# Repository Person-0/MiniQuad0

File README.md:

# **MiniQuad0**
Tiny Brushless Quadcopter, smaller and simpler version of Quad0.<br>
Custom flight controller with self-assembly in mind.

## 😼💖

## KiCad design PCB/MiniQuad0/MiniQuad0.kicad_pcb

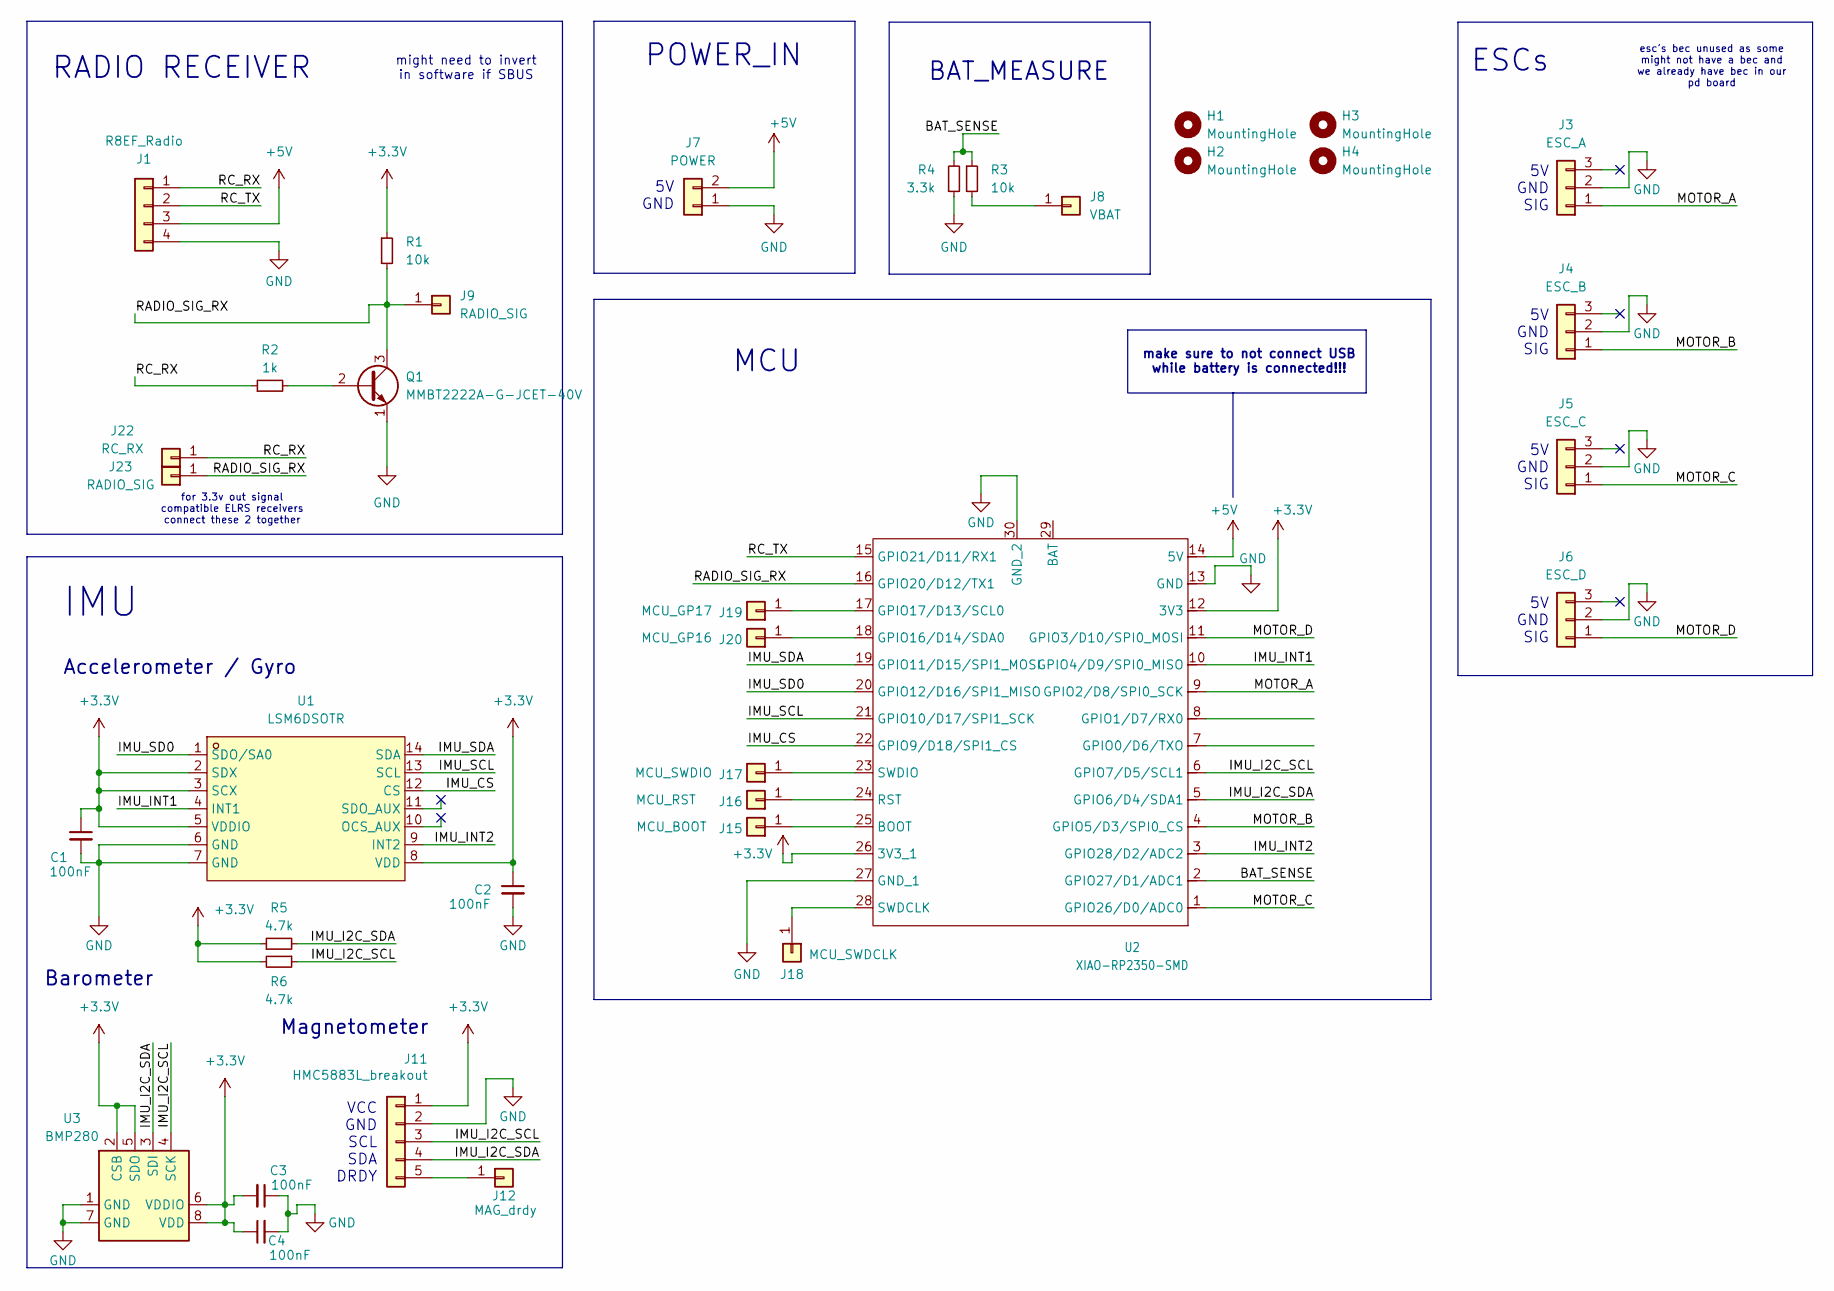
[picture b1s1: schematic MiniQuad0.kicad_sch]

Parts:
C1, C2, C3, C4: 100nF; C_0603_1608Metric_Pad1.08x0.95mm_HandSolder
H1, H2, H3, H4: MountingHole; MountingHole_3mm
J1: R8EF_Radio; PinHeader_1x04_P2.54mm_Vertical
J3: ESC_A; PinHeader_1x03_P2.54mm_Vertical
J4: ESC_B; PinHeader_1x03_P2.54mm_Vertical
J5: ESC_C; PinHeader_1x03_P2.54mm_Vertical
J6: ESC_D; PinHeader_1x03_P2.54mm_Vertical
J7: POWER; PinHeader_1x02_P2.54mm_Vertical
J8: VBAT; PinHeader_1x01_P2.54mm_Vertical
J9, J23: RADIO_SIG; TestPoint_Pad_D1.0mm
J11: HMC5883L_breakout; PinHeader_1x05_P2.54mm_Vertical
J12: MAG_drdy; TestPoint_Pad_D1.0mm
J15: MCU_BOOT; TestPoint_Pad_D1.0mm
J16: MCU_RST; TestPoint_Pad_D1.0mm
J17: MCU_SWDIO; TestPoint_Pad_D1.0mm
J18: MCU_SWDCLK; TestPoint_Pad_D1.0mm
J19: MCU_GP17; TestPoint_Pad_D1.0mm
J20: MCU_GP16; TestPoint_Pad_D1.0mm
J22: RC_RX; TestPoint_Pad_D1.0mm
Q1: MMBT2222A-G-JCET-40V; TSOT-23_HandSoldering
R1, R3: 10k; R_1206_3216Metric_Pad1.30x1.75mm_HandSolder
R2: 1k; R_1206_3216Metric_Pad1.30x1.75mm_HandSolder
R4: 3.3k; R_1206_3216Metric_Pad1.30x1.75mm_HandSolder
R5, R6: 4.7k; R_1206_3216Metric_Pad1.30x1.75mm_HandSolder
U1: LSM6DSOTR; LGA-14_L3.0-W2.5-P0.50-TL; MPN LSM6DSOTR; LCSC Part C2655100
U2: XIAO-RP2350-SMD
U3: BMP280; Bosch_LGA-8_2x2.5mm_P0.65mm_ClockwisePinNumbering

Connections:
+3.3V: C1.1, C2.1, C3.2, C4.1, J11.1, R1.1, R5.1, R6.2, U1.2 (SDX), U1.3 (SCX), U1.5 (VDDIO), U1.8 (VDD), U2.12 (3V3), U2.26 (3V3_1), U3.2 (CSB), U3.5 (SDO), U3.6 (VDDIO), U3.8 (VDD)
+5V: J1.3, J7.2, U2.14 (5V)
/BAT_SENSE: R3.1, R4.2, U2.2 (GPIO27/D1/ADC1)
/IMU_CS: U1.12 (CS), U2.22 (GPIO9/D18/SPI1_CS)
/IMU_I2C_SCL: J11.3, R6.1, U2.6 (GPIO7/D5/SCL1), U3.4 (SCK)
/IMU_I2C_SDA: J11.4, R5.2, U2.5 (GPIO6/D4/SDA1), U3.3 (SDI)
/IMU_INT1: U1.4 (INT1), U2.10 (GPIO4/D9/SPI0_MISO)
/IMU_INT2: U1.9 (INT2), U2.3 (GPIO28/D2/ADC2)
/IMU_SCL: U1.13 (SCL), U2.21 (GPIO10/D17/SPI1_SCK)
/IMU_SD0: U1.1 (SDO/SA0), U2.20 (GPIO12/D16/SPI1_MISO)
/IMU_SDA: U1.14 (SDA), U2.19 (GPIO11/D15/SPI1_MOSI)
/MOTOR_A: J3.1, U2.9 (GPIO2/D8/SPI0_SCK)
/MOTOR_B: J4.1, U2.4 (GPIO5/D3/SPI0_CS)
/MOTOR_C: J5.1, U2.1 (GPIO26/D0/ADC0)
/MOTOR_D: J6.1, U2.11 (GPIO3/D10/SPI0_MOSI)
/RADIO_SIG_RX: J9.1, J23.1, Q1.3 (C), R1.2, U2.16 (GPIO20/D12/TX1)
/RC_RX: J1.1, J22.1, R2.1
/RC_TX: J1.2, U2.15 (GPIO21/D11/RX1)
GND: C1.2, C2.2, C3.1, C4.2, J1.4, J3.2, J4.2, J5.2, J6.2, J7.1, J11.2, Q1.1 (E), R4.1, U1.6 (GND), U1.7 (GND), U2.13 (GND), U2.27 (GND_1), U2.30 (GND_2), U3.1 (GND), U3.7 (GND)
unnamed: J8.1, R3.2
unnamed: J11.5, J12.1
unnamed: J15.1, U2.25 (BOOT)
unnamed: J16.1, U2.24 (RST)
unnamed: J17.1, U2.23 (SWDIO)
unnamed: J18.1, U2.28 (SWDCLK)
unnamed: J19.1, U2.17 (GPIO17/D13/SCL0)
unnamed: J20.1, U2.18 (GPIO16/D14/SDA0)
unnamed: Q1.2 (B), R2.2

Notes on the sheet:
Accelerometer / Gyro
esc's bec unused as some might not have a bec and we already have bec in our pd board
IMU
Barometer
RADIO RECEIVER
make sure to not connect USB while battery is connected!!!
5V GND SIG
BAT_MEASURE
Magnetometer
POWER_IN
ESCs
MCU
for 3.3v out signal compatible ELRS receivers connect these 2 together
VCC GND SCL SDA DRDY
might need to invert in software if SBUS
5V GND

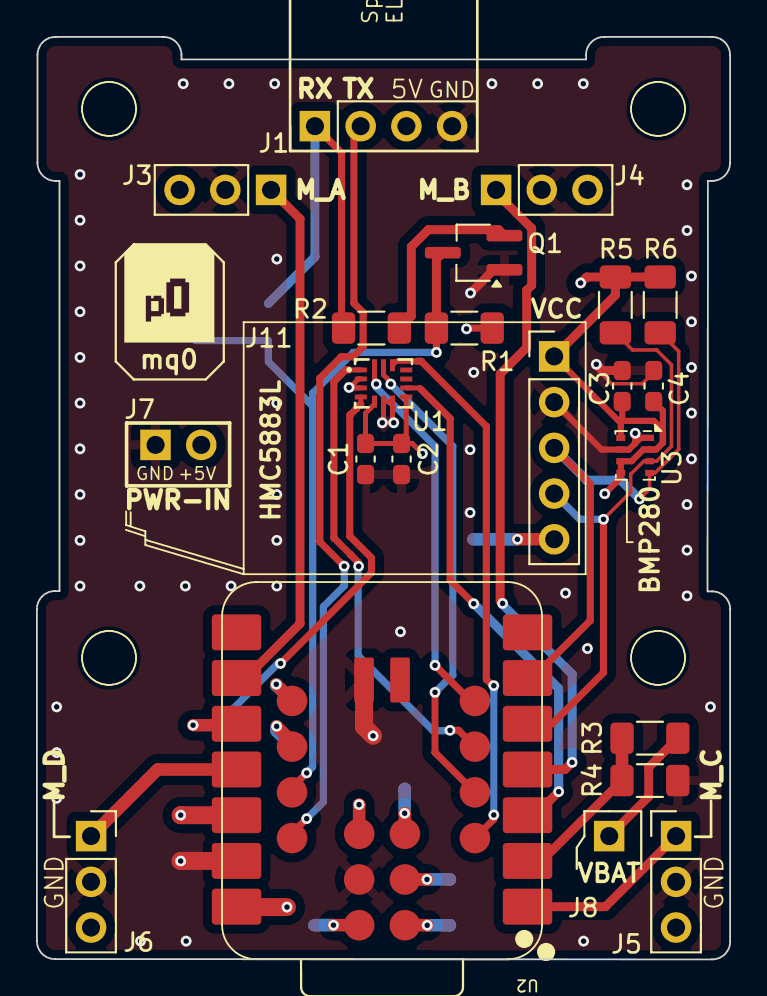
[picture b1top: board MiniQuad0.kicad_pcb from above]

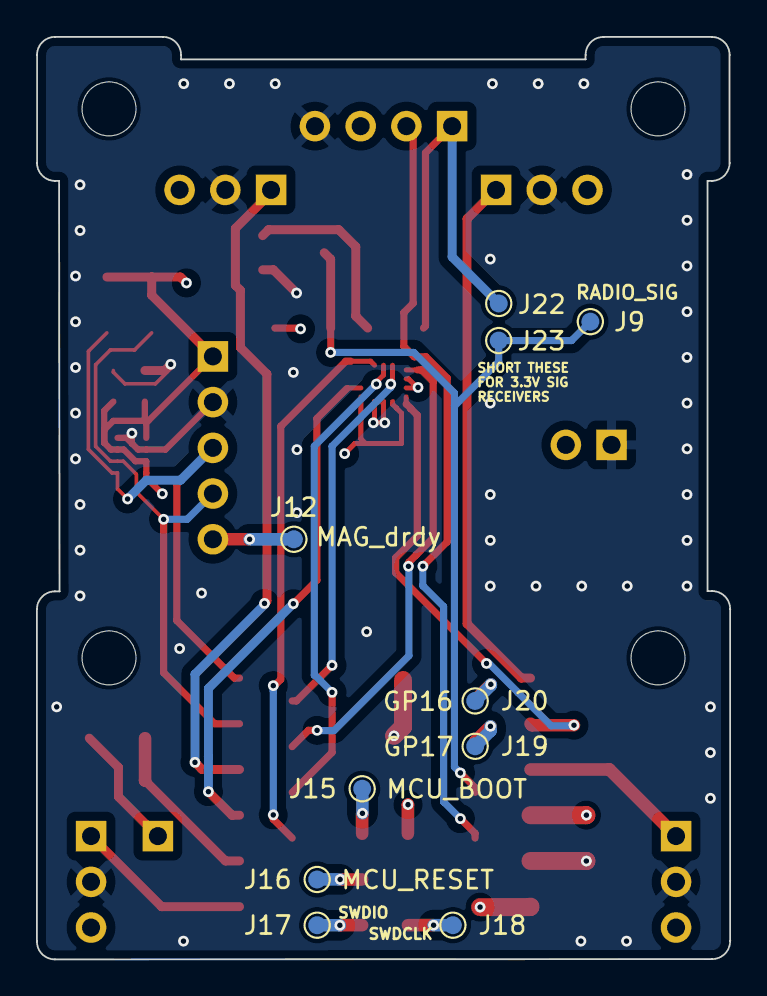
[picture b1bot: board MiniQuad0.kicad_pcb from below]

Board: 4 copper layers, 38.5 x 51.2 mm, 36 parts (10 on the bottom side), 28 nets.
